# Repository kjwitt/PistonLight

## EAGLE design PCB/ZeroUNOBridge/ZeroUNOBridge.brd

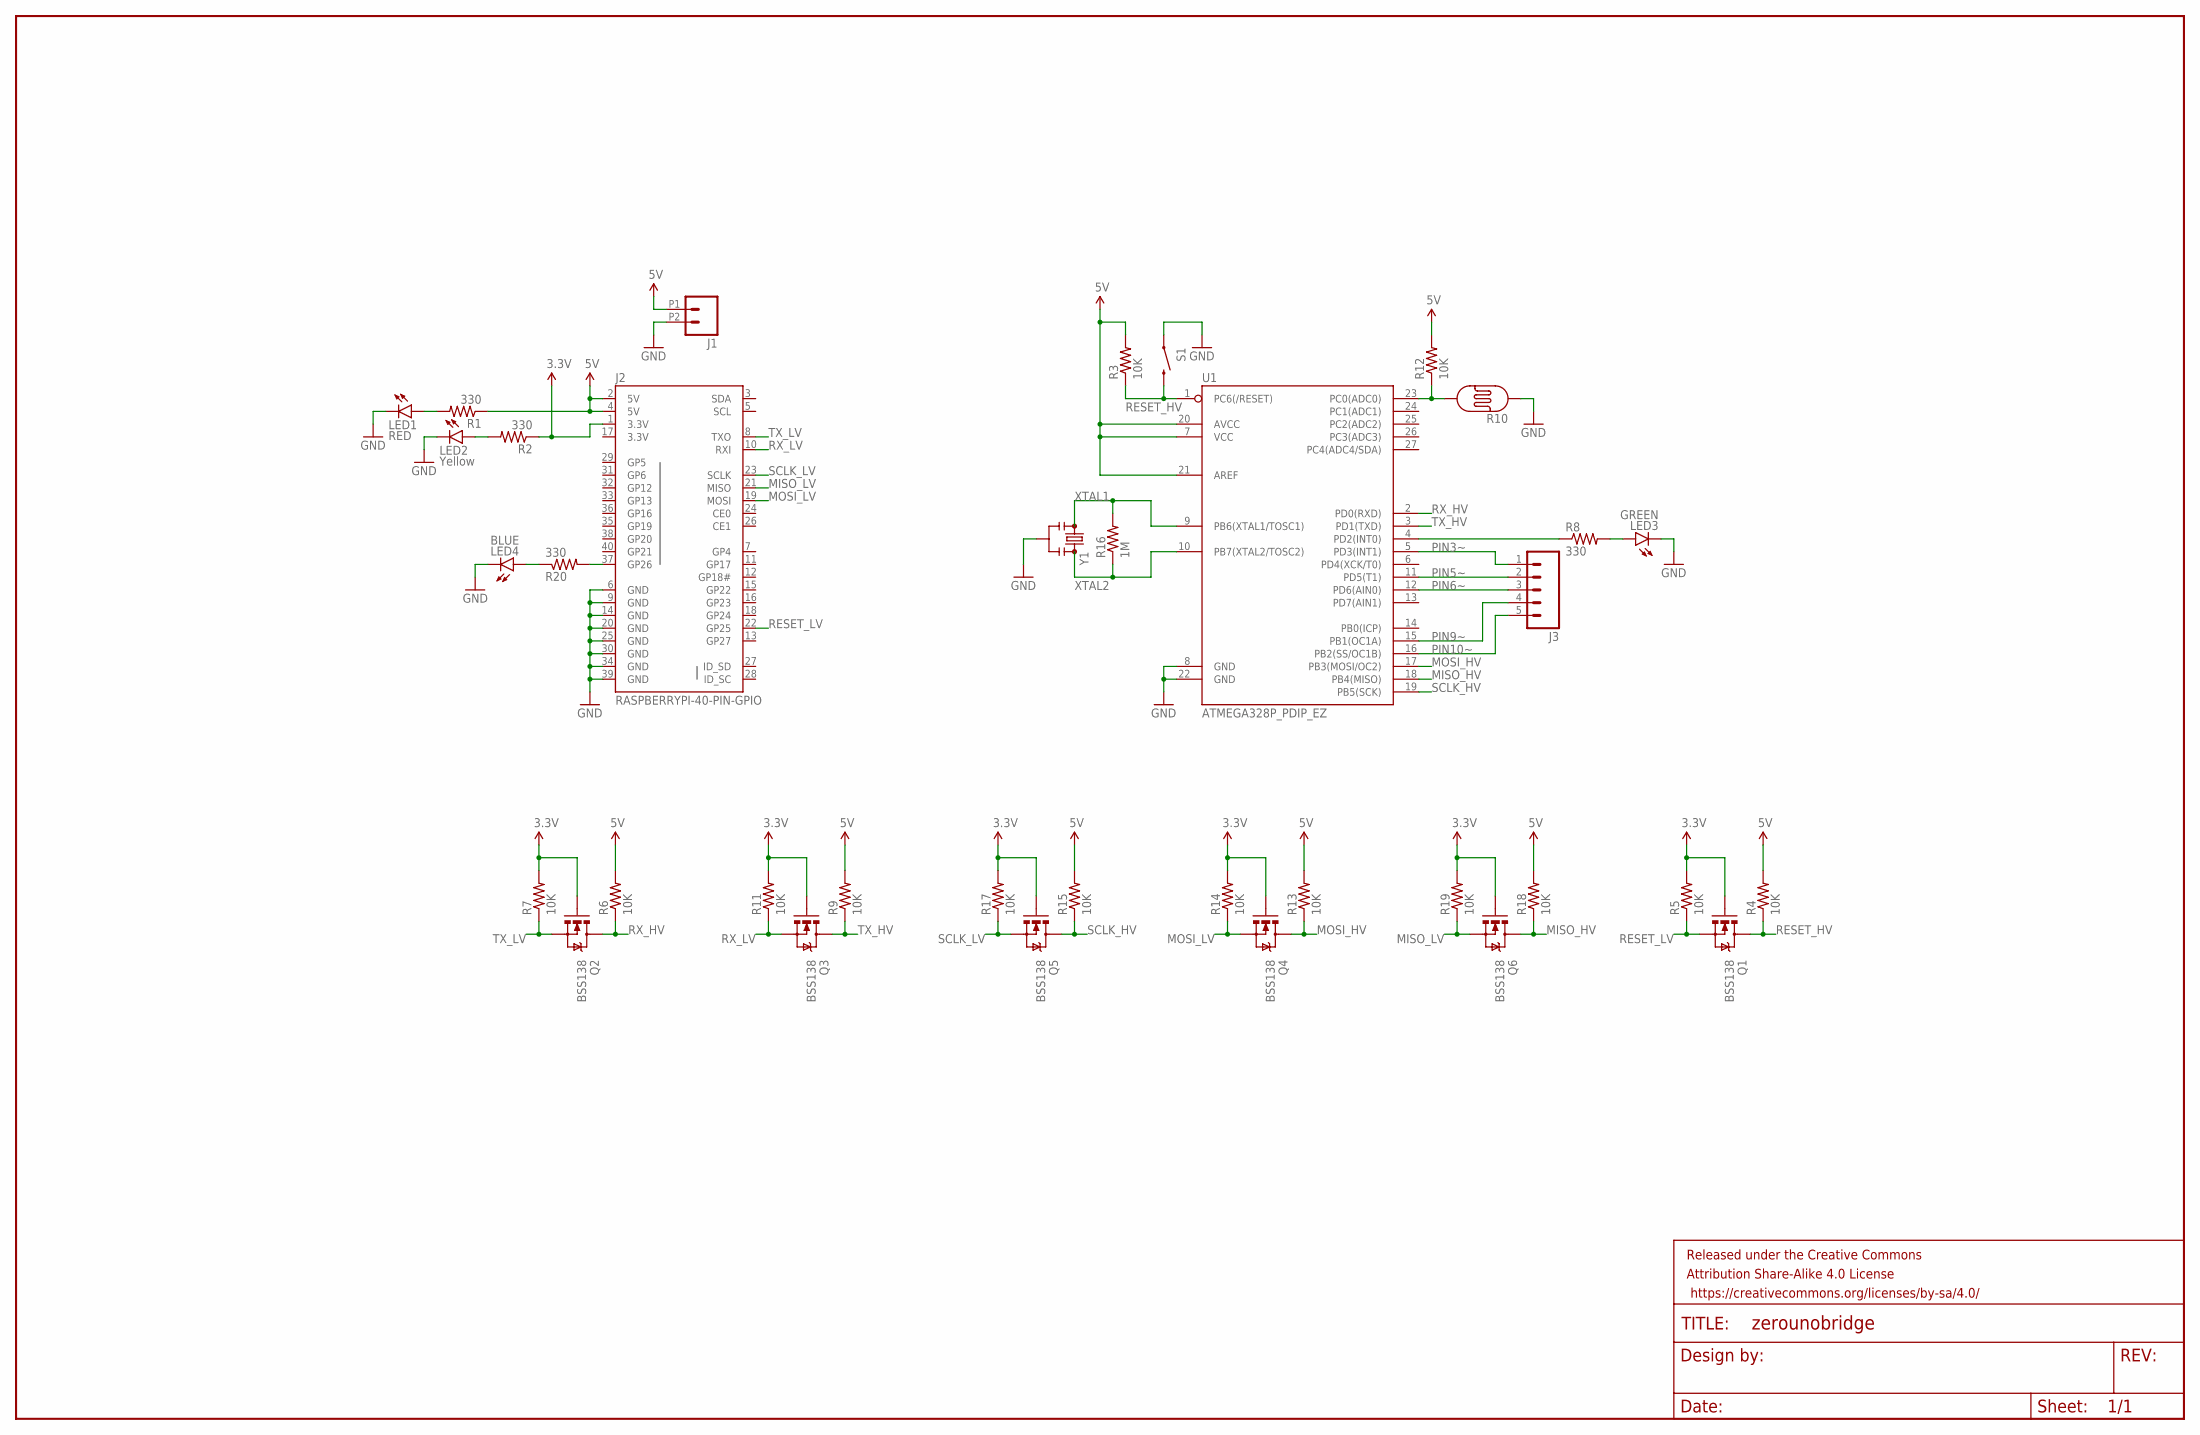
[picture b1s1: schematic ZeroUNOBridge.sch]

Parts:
FRAME1: FRAME-LEDGER; CREATIVE_COMMONS
J1: M022.54MM_SCREWTERM; 1X02_2.54_SCREWTERM
J2: RASPBERRYPI-40-PIN-GPIO; 2X20-SHROUDED
J3: M05SCREW; SCREWTERMINAL-3.5MM-5
LED1: RED; LED-0603
LED2: Yellow; LED-0603
LED3: GREEN; LED-0603
LED4: BLUE; LED-0603
Q1, Q2, Q3, Q4, Q5, Q6: BSS138; SOT23-3
R1, R2, R8, R20: 330; 0603-RES
R3, R4, R5, R6, R7, R9, R11, R12, R13, R14, R15, R17, R18, R19: 10K; 0603-RES
R10: PHOTOCELLPTH; PHOTOCELL
R16: 1M; 0603-RES
S1: SWITCH-MOMENTARY-2PTH; TACTILE-PTH
U1: ATMEGA328P_PDIP_EZ; DIL28-EZ
Y1: RESONATORPTH; RESONATOR-PTH

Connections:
3.3V: J2.1 (3.3V), J2.17 (3.3V), Q1.1 (G), Q2.1 (G), Q3.1 (G), Q4.1 (G), Q5.1 (G), Q6.1 (G), R2.1, R5.2, R7.2, R11.2, R14.2, R17.2, R19.2
5V: J1.P1 (1), J2.2 (5V), J2.4 (5V), R1.1, R3.2, R4.2, R6.2, R9.2, R12.2, R13.2, R15.2, R18.2, U1.7 (VCC), U1.20 (AVCC), U1.21 (AREF)
GND: J1.P2 (2), J2.6 (GND), J2.9 (GND), J2.14 (GND), J2.20 (GND), J2.25 (GND), J2.30 (GND), J2.34 (GND), J2.39 (GND), LED1.C, LED2.C, LED3.C, LED4.C, R10.1, S1.1, U1.8 (GND), U1.22 (GND), Y1.2
MISO_HV: Q6.3 (D), R18.1, U1.18 (PB4(MISO))
MISO_LV: J2.21 (MISO), Q6.2 (S), R19.1
MOSI_HV: Q4.3 (D), R13.1, U1.17 (PB3(MOSI/OC2))
MOSI_LV: J2.19 (MOSI), Q4.2 (S), R14.1
unnamed: J2.37 (GP26), R20.2
unnamed: LED1.A, R1.2
unnamed: LED2.A, R2.2
unnamed: LED4.A, R20.1
unnamed: R8.1, U1.4 (PD2(INT0))
unnamed: LED3.A, R8.2
unnamed: R10.2, R12.1, U1.23 (PC0(ADC0))
PIN3~: J3.1, U1.5 (PD3(INT1))
PIN5~: J3.2, U1.11 (PD5(T1))
PIN6~: J3.3, U1.12 (PD6(AIN0))
PIN9~: J3.4, U1.15 (PB1(OC1A))
PIN10~: J3.5, U1.16 (PB2(SS/OC1B))
RESET_HV: Q1.3 (D), R3.1, R4.1, S1.3 (2), U1.1 (PC6(/RESET))
RESET_LV: J2.22 (GP25), Q1.2 (S), R5.1
RX_HV: Q2.3 (D), R6.1, U1.2 (PD0(RXD))
RX_LV: J2.10 (RXI), Q3.2 (S), R11.1
SCLK_HV: Q5.3 (D), R15.1, U1.19 (PB5(SCK))
SCLK_LV: J2.23 (SCLK), Q5.2 (S), R17.1
TX_HV: Q3.3 (D), R9.1, U1.3 (PD1(TXD))
TX_LV: J2.8 (TXO), Q2.2 (S), R7.1
XTAL1: R16.2, U1.9 (PB6(XTAL1/TOSC1)), Y1.1
XTAL2: R16.1, U1.10 (PB7(XTAL2/TOSC2)), Y1.3

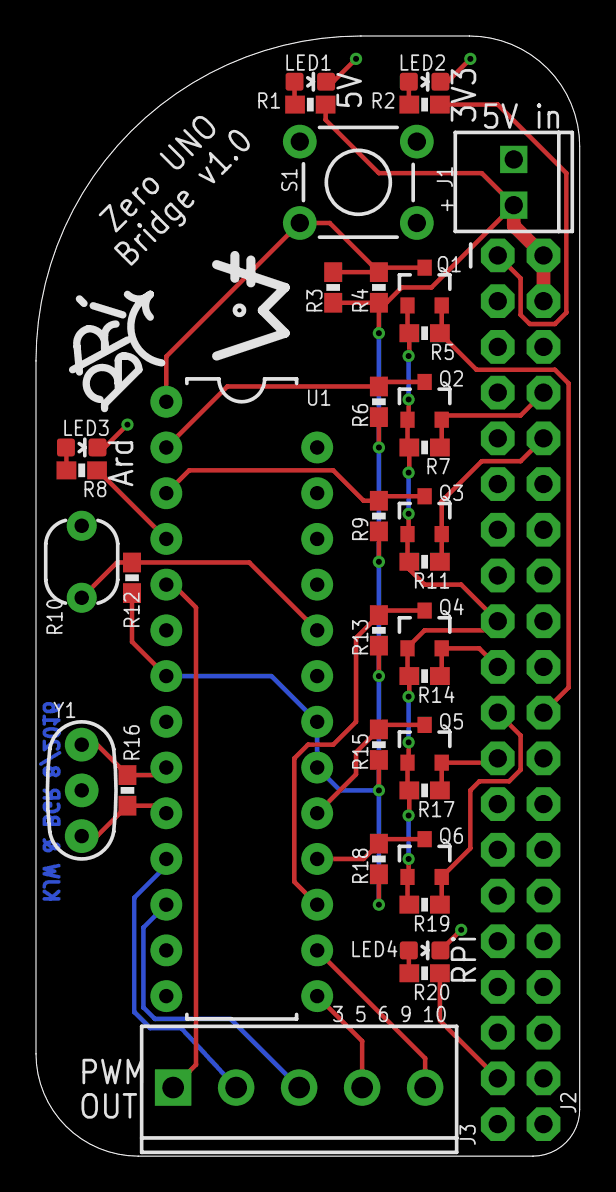
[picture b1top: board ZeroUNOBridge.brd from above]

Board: 2 copper layers, 30.2 x 62.2 mm, 37 parts (0 on the bottom side), 29 nets.

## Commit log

2016-07-24 Initial Board Design
2016-07-24 Routing Traces
    -Initial routing of traces
    -Correcting component labels
2016-07-24 Added Power Jack
    -Changed RPi port to compensate
    -Adjusted labels
    -Added tag
    -Added initials
2016-07-25 Final Labeling Corrections
    -Labeling jacks
    -Added tag
2016-07-25 Moved board width inwards
    Should move left side in a bit as well
2016-07-25 Misc Fixes
    -Made board dimensions smaller
    -Moved Bri's tag
    -Actually connected up the SPI clock
    -Moved 3.3V LED to other 3.3V port on RPi header
2016-08-11 Added level translators so the RPi doesn't blow up
    pretty much redid the entire thing - many conversions to SMD
2016-08-11 Fixed Text Issues
2016-08-11 Final Changes
    -DRC clear
    -Renumber
2016-08-11 Increased DRC distances
    because paranoia

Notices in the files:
parts and their libraries:
SparkFun-Boards: Licensing: Creative Commons ShareAlike 4.0 International - https://creativecommons.org/licenses/by-sa/4.0
SparkFun-Aesthetics: Released under the Creative Commons Attribution Share-Alike 4.0 License
SparkFun-Aesthetics: https://creativecommons.org/licenses/by-sa/4.0
